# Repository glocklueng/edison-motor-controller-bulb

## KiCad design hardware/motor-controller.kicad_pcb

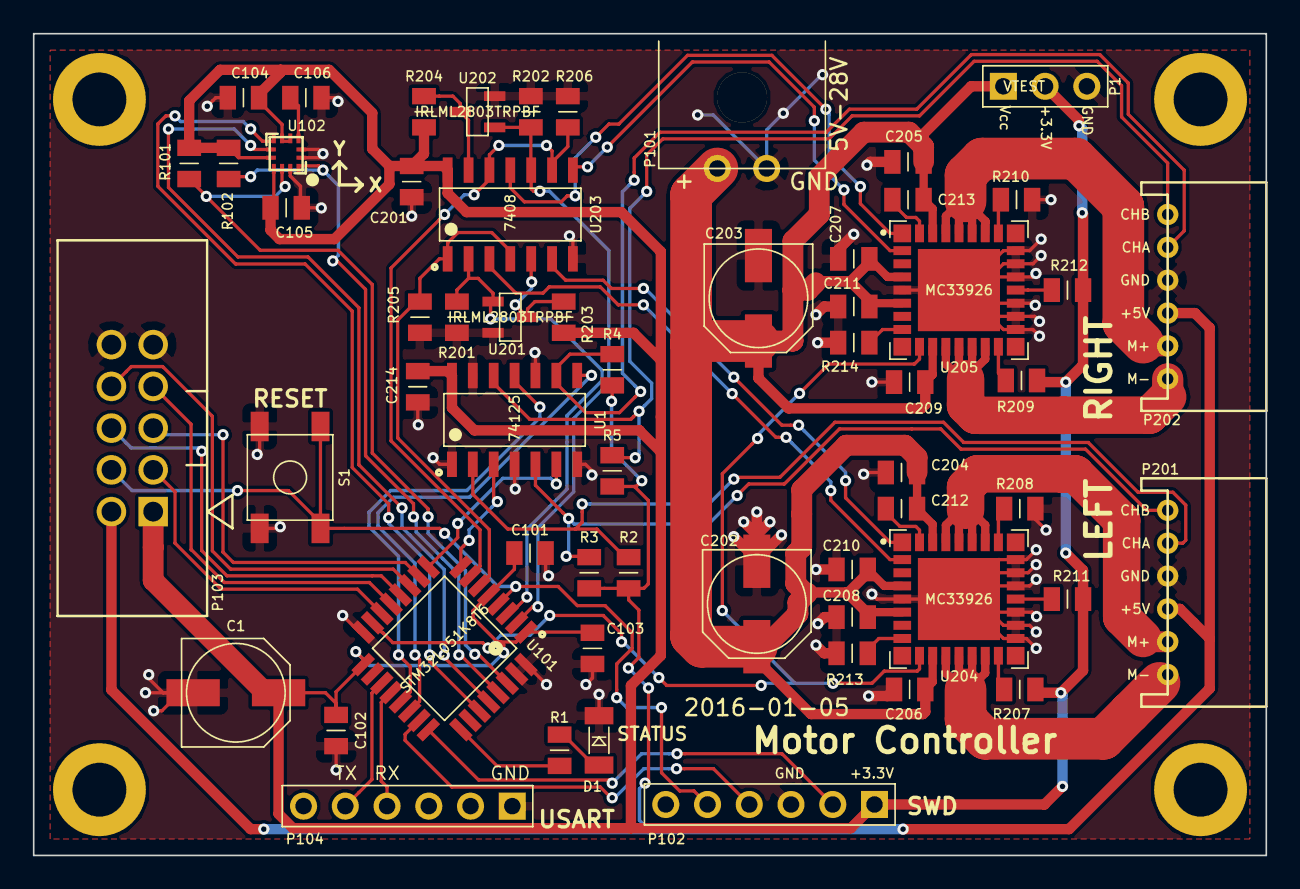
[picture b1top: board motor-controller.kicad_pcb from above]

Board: 2 copper layers, 75.0 x 50.0 mm, 63 parts (0 on the bottom side), 54 nets.

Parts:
C1: 100uF; CAPAE660X790N
C101, C102, C103, C105, C106, C201, C214: 0.1uF; CAPC2012X100N
C104: 1uF; CAPC2012X100N
C202, C203: 100uF 35V; CAPAE660X790N
C204, C205, C206, C207, C208, C209, C210, C211: 0.1uF 35V; CAPC2012X100N
C212, C213: 33nF 35V; CAPC2012X100N
D1: STATUS; LEDC3216X100N
M1, M2, M3, M4: Mounting Hole; MTGNP565H328Z565P
P1: VTEST; HDRV3W66P254_1X3_762X249X838P
P101: BATTERY; TECONN-2-1445098-2
P102: SWD; HDRV6W66P254_1X6_1524X249X838P
P103: EDISON-BULB-E10; SHDRV10W66P254_2X5_2286X910X910P
P104: FTDI-PLUG; HDRV6W66P254_1X6_1524X249X838P
P201, P202: P06-MOTOR; JST-S6B-PH-K
R1: 100R; RESC2012X100N
R2, R3, R4, R5: 1K; RESC2012X100N
R101, R102: 4.7K; RESC2012X100N
R201, R202, R203, R204, R205, R206, R207, R208, R209, R210, R211, R212: 10K; RESC2012X100N
R213, R214: 270R; RESC2012X100N
S1: RESET; CKCOMP-PTS525SM10SMTR
U1: 74125; SOIC127P600X175-14N
U101: STM32L051K8T6; QFP80P900X900X160-32N
U102: ST-LIS3MDL; LGA12S50P4X4_192X192X100
U201, U202: IRLML2803TRPBF; SOT95P237X112_123-3N
U203: 7408; SOIC127P600X175-14N
U204, U205: MC33926; PQFN80P800X800X220-33N

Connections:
+3.3V: C1.1, C101.1, C102.1, C103.1, C104.1, C105.1, C201.1, C214.1, P1.2, P102.1, P103.1, R101.1, R102.1, R203.1, R204.1, R207.1, R209.1, R211.1, R212.1, U1.14, U101.1, U101.5, U101.17, U102.5, U102.6, U102.9, U102.10, U203.14
+5V: P103.2, P201.3, P202.3, R2.1, R3.1, R4.1, R5.1
/COMPASSDRDY: U101.28, U102.8
/COMPASSINT: U101.27, U102.7
/I2CSCL: R102.2, U101.29, U102.1
/I2CSDA: R101.2, U101.30, U102.11
/NIRQ: P103.3, U101.14
/NRST: P102.5, P103.4, S1.3, S1.4, U101.4
/SPICS: P103.5, U101.10
/SPIMISO: P103.6, U101.12
/SPIMOSI: P103.7, U101.13
/SPISCK: P103.8, U101.11
/STATUS: R1.2, U101.25
/SWCLK: P102.2, U101.24
/SWDIO: P102.4, U101.23
/USARTRX: P104.4, U101.20
/USARTTX: P104.5, U101.19
/drivers/MOTOREN: U101.15, U204.10, U205.10
/drivers/MOTORL+: P201.2, U204.27, U204.28, U204.29, U204.30
/drivers/MOTORL-: P201.1, U204.12, U204.13, U204.14, U204.15
/drivers/MOTORLCHA: U1.3, U101.8
/drivers/MOTORLCHB: U1.6, U101.9
/drivers/MOTORLDIR: R201.1, U101.3, U201.1, U203.2
/drivers/MOTORLOUTCHA: P201.5, R2.2, U1.2
/drivers/MOTORLOUTCHB: P201.6, R3.2, U1.5
/drivers/MOTORLPWM: R205.1, U101.6, U203.1, U203.4
/drivers/MOTORR+: P202.2, U205.27, U205.28, U205.29, U205.30
/drivers/MOTORR-: P202.1, U205.12, U205.13, U205.14, U205.15
/drivers/MOTORRCHA: U1.8, U101.22
/drivers/MOTORRCHB: U1.11, U101.21
/drivers/MOTORRDIR: R202.1, U101.2, U202.1, U203.10
/drivers/MOTORROUTCHA: P202.5, R4.2, U1.9
/drivers/MOTORROUTCHB: P202.6, R5.2, U1.12
/drivers/MOTORRPWM: R206.1, U101.7, U203.9, U203.12
GNDPWR: C1.2, C101.2, C102.2, C103.2, C104.2, C105.2, C106.2, C201.2, C202.2, C203.2, C204.2, C205.2, C206.2, C207.2, C208.2, C209.2, C210.2, C211.2, C214.2, D1.2, P1.3, P101.2, P102.3, P103.9, P103.10, P104.1, P201.4, P202.4, R201.2, R202.2, R205.2, R206.2, R208.2, R210.2, R213.2, R214.2, S1.1, S1.2, U1.1, U1.4, U1.7, U1.10, U1.13, U101.16, U101.31, U101.32, U102.2, U102.3, U102.12, U201.2, U202.2, U203.7, U204.5, U204.18, U204.19, U204.20, U204.22, U204.23, U204.24, U204.33, U205.5, U205.18, U205.19, U205.20, U205.22, U205.23, U205.24, U205.33
unnamed: C106.1, U102.4
unnamed: C212.2, U204.32
unnamed: C213.2, U205.32
unnamed: D1.1, R1.1
unnamed: R203.2, U201.3, U203.5
unnamed: R204.2, U202.3, U203.13
unnamed: R207.2, U204.16
unnamed: R208.1, U204.26
unnamed: R209.2, U205.16
unnamed: R210.1, U205.26
unnamed: R211.2, U204.21
unnamed: R212.2, U205.21
unnamed: R213.1, U204.8
unnamed: R214.1, U205.8
unnamed: U203.3, U204.2
unnamed: U203.6, U204.1
unnamed: U203.8, U205.2
unnamed: U203.11, U205.1
Vcc: C202.1, C203.1, C204.1, C205.1, C206.1, C207.1, C208.1, C209.1, C210.1, C211.1, C212.1, C213.1, P1.1, P101.1, U204.4, U204.6, U204.11, U204.31, U205.4, U205.6, U205.11, U205.31

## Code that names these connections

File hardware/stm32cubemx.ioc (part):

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Mcu.Name=STM32F030K6Tx
Mcu.Package=LQFP32
Mcu.UserName=STM32F030K6Tx
PA1.GPIOParameters=GPIO_Label
PA1.GPIO_Label=IRQ
PA1.Signal=GPIO_Output
PA10.GPIOParameters=GPIO_Label
PA10.GPIO_Label=MOTORRPWM
PA10.Signal=S_TIM1_CH3
PA11.GPIOParameters=GPIO_Label
PA11.GPIO_Label=MOTORRDIR
PA11.Signal=GPIO_Output
PA12.GPIOParameters=GPIO_Label
PA12.GPIO_Label=MOTOREN
PA12.Signal=GPIO_Output
PA13.Mode=Serial-WireDebug
PA13.Signal=SYS_SWDIO
PA14.Mode=Serial-WireDebug
PA14.Signal=SYS_SWCLK
PA15.GPIOParameters=GPIO_Label
PA15.GPIO_Label=COMPASSDRDY
PA15.Signal=GPIO_Input
PA2.Mode=Asynchronous
PA2.Signal=USART1_TX
PA3.Mode=Asynchronous
PA3.Signal=USART1_RX
PA4.Mode=NSS_Signal_Hard
PA4.Signal=SPI1_NSS
PA5.Mode=Full_Duplex_Slave
PA5.Signal=SPI1_SCK
PA6.Mode=Full_Duplex_Slave
PA6.Signal=SPI1_MISO
PA7.Mode=Full_Duplex_Slave
PA7.Signal=SPI1_MOSI
PA8.GPIOParameters=GPIO_Label
PA8.GPIO_Label=MOTORLPWM
PA8.Signal=S_TIM1_CH1
PA9.GPIOParameters=GPIO_Label
PA9.GPIO_Label=MOTORLDIR
PA9.Signal=GPIO_Output
PB0.GPIOParameters=GPIO_Label
PB0.GPIO_Label=MOTORRCHA
PB0.Signal=GPIO_Input
PB1.GPIOParameters=GPIO_Label
PB1.GPIO_Label=MOTORRCHB
PB1.Signal=GPIO_Input
PB3.GPIOParameters=GPIO_Label
PB3.GPIO_Label=COMPASSINT
PB3.Signal=GPIO_Input
PB4.GPIOParameters=GPIO_Label
PB4.GPIO_Label=MOTORLCHB
PB4.Signal=GPIO_Input
PB5.GPIOParameters=GPIO_Label
PB5.GPIO_Label=MOTORLCHA
PB5.Signal=GPIO_Input
PB6.Mode=I2C
PB6.Signal=I2C1_SCL
PB7.Mode=I2C
PB7.Signal=I2C1_SDA

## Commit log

2015-07-25 initial
2015-07-25 add footprints for motor connectors
2015-07-25 add package for battery and compass
2015-07-25 initial component placement
2015-07-26 initial layout
2015-07-26 more layout
2015-07-27 first cut
2015-08-01 rework layout
2015-11-12 initial firmware
2015-11-12 initial compile
2015-11-13 gerbers 2015-11-12
2015-11-13 include edge cuts
2015-11-16 initial SPI coms working
2015-11-16 add test firmware
2015-11-18 working spi
2015-11-21 format code
2015-11-21 motor encoder
2015-11-22 work on lis3mdl
2015-11-25 remove unused ioc file
2015-11-25 add edison-driver.js
2015-11-26 initial driver and client
2015-11-29 new hardware
2015-11-29 working reads of lis3mdl
2015-11-29 working compass
2015-11-30 working pwm
2015-12-01 working motor encoder
2015-12-01 move update encoders to contiki process
2015-12-09 getting further
2015-12-09 use HAL_FLASHEx_Erase
2015-12-10 more bootloader work
2015-12-11 working bootloader
2015-12-12 update makefile
2015-12-12 working irq
2015-12-14 bootloader check crc32
2015-12-16 move bootloader to new repo
2015-12-19 rotate wheels in opposite directions to go forward
2015-12-24 switch to rotation instead of header
2015-12-24 almost working rotation
2015-12-24 don't reduce speed
2015-12-27 change tim1 prescaler
2015-12-27 change printf to debug
2015-12-27 save/load settings from eeprom
2015-12-27 format files
2016-01-03 change pinout and add pullup resistor
2016-01-03 add reset button
2016-01-03 layout
2016-01-05 compass x/y
2016-01-09 increase lead size of LGA
2016-01-09 update gerbers for manufacture
